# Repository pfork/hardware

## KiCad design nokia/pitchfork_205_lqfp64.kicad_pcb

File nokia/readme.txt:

cc0 licensed PITCHFORK board in nokia3310 formfactor

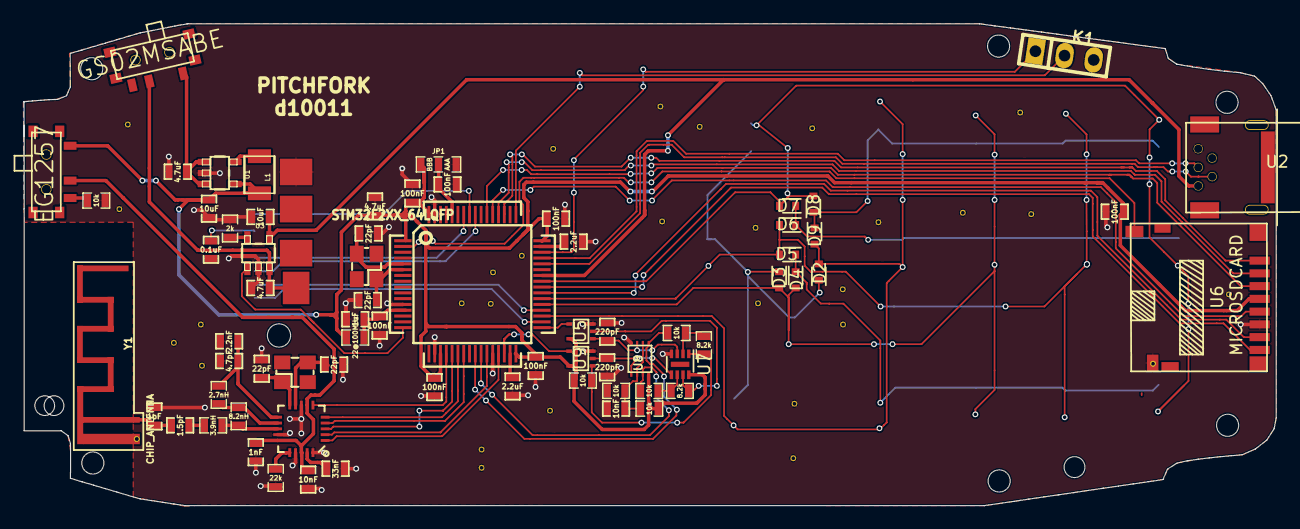
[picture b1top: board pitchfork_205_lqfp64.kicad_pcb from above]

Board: 2 copper layers, 108.0 x 41.5 mm, 100 parts (1 on the bottom side), 67 nets.

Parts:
1Pin_12mil_VIA, 1Pin_12mil_VIA#2, 1Pin_12mil_VIA#3, 1Pin_12mil_VIA#4, 1Pin_12mil_VIA#5, 1Pin_12mil_VIA#6, 1Pin_12mil_VIA#7, 1Pin_12mil_VIA#8, 1Pin_12mil_VIA#9, 1Pin_12mil_VIA#10, 1Pin_12mil_VIA#11, 1Pin_12mil_VIA#12, 1Pin_12mil_VIA#13, 1Pin_12mil_VIA#14, 1Pin_12mil_VIA#15, 1Pin_12mil_VIA#16, 1Pin_12mil_VIA#17, 1Pin_12mil_VIA#18, 1Pin_12mil_VIA#19, 1Pin_12mil_VIA#20, 1Pin_12mil_VIA#21, 1Pin_12mil_VIA#22, 1Pin_12mil_VIA#23, 1Pin_12mil_VIA#24, 1Pin_12mil_VIA#25, 1Pin_12mil_VIA#26, 1Pin_12mil_VIA#27, 1Pin_12mil_VIA#28, 1Pin_12mil_VIA#29: VAL**; 1Pin_12mil_VIA
B1: 3310
C1, C2, C25, C26: 22pF; SM0603_Opendous
C3, C4, C9, C10, C11, C14, C34: 100nF; SM0603_Opendous
C5, C6, C13: 4.7uF; SM0603_Opendous
C7, C8: 2.2uF; SM0603_Opendous
C12, C20: 10uF; SM0603_Opendous
C15: 1uF; SM0603_Opendous
C16, C19: 10nF; SM0603_Opendous
C17: 1nF; SM0603_Opendous
C18: 0.1uF; SM0603_Opendous
C21: 33nF; SM0603_Opendous
C22: 1pF; SM0603_Opendous
C23: 1.5pF; SM0603_Opendous
C24: 4.7pF; SM0603_Opendous
C27: 2.2nF; SM0603_Opendous
C28, C29: 220pF; SM0603_Opendous
D2, D3, D4, D5, D6, D7, D8, D9: 1N5148; SOD-523
IC1: STM32F2XX_64LQFP; LQFP64_Opendous
JP1: JUMPER3; 0603_Jumper
K1: CONN_3; pin_strip_3
L1: 10uH; SparkFun-1210
L2: 22@100MHz; 0603_Opendous
L5: 3.9nH; 0603_Opendous
L6: 8.2nH; 0603_Opendous
L7: 2.7nH; 0603_Opendous
R1, R5, R6, R9, R10, R11: 10k; 0603_Opendous
R3: 2k; 0603_Opendous
R4: 22k; 0603_Opendous
R7, R8: 8.2k; 0603_Opendous
SW_POWER1: GS02MSABE; EG1257
SW_RFPWR1: EG1257
U1: LM3670; SparkFun-SOT23-5
U2: USBCONN; miniusb
U3: MCP73832-2; SparkFun-SOT23-5
U4: NRF24L01+; QFN20_0.5mmPitch_HMC5843
U5, U9: MC74VHC1G66; SOT-353
U6: MICROSDCARD; HiroseDM3D-SF
U7: TSV912; DFN-8-1EP_2x2mm_Pitch0.5mm
U8: TC75W57; SSOP8-P0.5
X1: 25MHz; Crystal_3.2x2.5mm
X2: 16MHz; Crystal_3.2x2.5mm
Y1: CHIP_ANTENNA; Antenna_Meander_2.4GHz_TI_AN043

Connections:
/B0I: B1.25, B1.45, B1.47, B1.49, D7.2, D8.2, IC1.41
/B0O: B1.30, B1.36, B1.42, B1.46, D6.1, D7.1
/B1I: B1.19, B1.27, B1.29, B1.31, D2.2, D9.2, IC1.35
/B1O: B1.28, B1.34, B1.40, B1.50, D8.1, D9.1
/B3O: B1.32, B1.38, B1.44, B1.48, D4.1, D5.1
/B4I: B1.21, B1.33, B1.35, B1.37, D3.2, D4.2, IC1.37
/B7I: B1.23, B1.39, B1.41, B1.43, D5.2, D6.2, IC1.38
/BCO: B1.20, B1.22, B1.24, B1.26, D2.1, D3.1
/CHRG_STAT: IC1.16, U3.1
/LCD_CS: B1.13, IC1.58
/LCD_DC: B1.12, IC1.56
/LCD_RES: B1.16, IC1.57
/LCD_SCLK: B1.10, IC1.34
/LCD_SDIN: B1.11, IC1.36
/VBAT: C6.1, SW_POWER1.1, U1.1, U1.3
/VBAT0: B1.5, C5.1, SW_POWER1.2, U3.3
/comp1: IC1.25, R6.2, U8.1
/comp2: IC1.26, R9.2, U8.7
/nrf_ce: IC1.29, U4.1
/nrf_csn: IC1.27, U4.2
/nrf_irq: IC1.20, U4.6
/nrf_miso: IC1.22, U4.5
/nrf_mosi: IC1.23, U4.4
/nrf_sck: IC1.21, U4.3
/rswen1: IC1.33, U5.4
/rswen2: IC1.30, U9.4
/sd_cd: IC1.2, U6.10
/sd_clk: IC1.53, U6.5
/sd_cmd: IC1.54, U6.3
/sd_d0: IC1.39, U6.7
/sd_d1: IC1.40, U6.8
/sd_d2: IC1.51, U6.1
/sd_d3: IC1.52, U6.2
/swclk: IC1.49, K1.2
/swdio: IC1.46, K1.1
/usb_5v: C20.1, IC1.42, U2.1, U3.4
/usb_dm: IC1.44, U2.2
/usb_dp: IC1.45, U2.3
/vdd: B1.9, C4.1, C9.2, C10.2, C11.2, C12.1, C13.2, C34.2, IC1.1, IC1.19, IC1.32, IC1.48, IC1.64, JP1.3, L1.2, L2.2, R1.2, R10.1, SW_RFPWR1.2, U1.4, U5.5, U6.4, U7.8, U8.8, U9.5
GND: 1Pin_12mil_VIA.1, 1Pin_12mil_VIA#2.1, 1Pin_12mil_VIA#3.1, 1Pin_12mil_VIA#4.1, 1Pin_12mil_VIA#5.1, 1Pin_12mil_VIA#6.1, 1Pin_12mil_VIA#7.1, 1Pin_12mil_VIA#8.1, 1Pin_12mil_VIA#9.1, 1Pin_12mil_VIA#10.1, 1Pin_12mil_VIA#11.1, 1Pin_12mil_VIA#12.1, 1Pin_12mil_VIA#13.1, 1Pin_12mil_VIA#14.1, 1Pin_12mil_VIA#15.1, 1Pin_12mil_VIA#16.1, 1Pin_12mil_VIA#17.1, 1Pin_12mil_VIA#18.1, 1Pin_12mil_VIA#19.1, 1Pin_12mil_VIA#20.1, 1Pin_12mil_VIA#21.1, 1Pin_12mil_VIA#22.1, 1Pin_12mil_VIA#23.1, 1Pin_12mil_VIA#24.1, 1Pin_12mil_VIA#25.1, 1Pin_12mil_VIA#26.1, 1Pin_12mil_VIA#27.1, 1Pin_12mil_VIA#28.1, 1Pin_12mil_VIA#29.1, B1.8, B1.14, B1.17, B1.18, C1.1, C2.1, C3.2, C4.2, C5.2, C6.2, C7.2, C8.2, C9.1, C10.1, C11.1, C12.2, C13.1, C14.2, C15.2, C16.2, C17.2, C18.2, C19.2, C20.2, C21.1, C22.1, C24.1, C25.2, C26.2, C27.1, C28.2, C29.2, C34.1, IC1.12, IC1.18, IC1.28, IC1.63, JP1.1, K1.3, R3.2, R4.1, R5.2, R11.1, U1.2, U2.5, U3.2, U4.8, U4.14, U4.17, U4.20, U5.3, U6.6, U6.9, U7.4, U8.4, U9.3
unnamed: B1.15, C18.1
unnamed: C1.2, IC1.5, X1.2
unnamed: C2.2, IC1.6, X1.1
unnamed: C3.1, IC1.60, JP1.2
unnamed: C7.1, IC1.31
unnamed: C8.1, IC1.47
unnamed: C14.1, C15.1, IC1.13, L2.1
unnamed: C16.1, C17.1, SW_RFPWR1.1, U4.7, U4.15, U4.18
unnamed: C19.1, R1.1, R5.1, U8.2, U8.6
unnamed: C21.2, U4.19
unnamed: C22.2, C23.1, Y1.1
unnamed: C23.2, L5.1
unnamed: C24.2, C27.2, L7.2, U4.11
unnamed: C25.1, U4.9, X2.2
unnamed: C26.1, U4.10, X2.1
unnamed: C28.1, U5.1, U7.3, U8.3
unnamed: C29.1, U7.5, U8.5, U9.2
unnamed: L1.1, U1.5
unnamed: L5.2, L6.2, U4.13
unnamed: L6.1, L7.1, U4.12
unnamed: R3.1, U3.5
unnamed: R4.2, U4.16
unnamed: R6.1, R7.2, U7.2
unnamed: R8.1, U5.2, U7.7
unnamed: R8.2, R9.1, U7.6
unnamed: R7.1, R10.2, U7.1, U9.1
unnamed: R11.2, SW_RFPWR1.3

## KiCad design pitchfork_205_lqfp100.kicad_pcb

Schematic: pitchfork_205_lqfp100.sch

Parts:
BT1: BATTERY_LI-ION
C1: 4.7uF
C2, C22: 10uF
C3, C20: 22p
C4, C15, C16, C17, C18, C19, C25, C27, C29: 100n
C5: 100n
C6, C7, C30: 100nF
C21: 4.7u
C23, C24: 2.2u
C26, C28: 1u
C31: 10pF
C32: 33nF
C33, C34: 22pF
C35: CSMALL
C36: 1.5pF
C37: 4.7pF
C38: 2.2nF
C39, C41, C43: 2.2uF
C40, C42: 0.1uF
D1: SML-211UTT86
D2: SML-211YTT86
D3, D4: SML-211UTT86
JP2: JUMPER
L1: 30@100MHz
L2: 22@100MHz
L3: FERRITE
L4: 3.9nH
L5: 8.2nH
L6: 2.7nH
L7: 10uH
P1: SD_CARD
R1, R2: 1k
R3: R1002-1%63
R4: 22k
R6: 2k
R7: 560k
R13, R14: 1k
SW1, SW2, SW3, SW4: SW_PUSH
SW5: SWITCH_PUSHBUTTON
U1: STM32F205Vxx
U2: NRF24L01+
U3: USBCONN
U4: LM3670
U5: MCP73832-2
U6: UG-2864H
X1: CRYSTAL
X2: 3.2x2.5
Y1: CHIP_ANTENNA

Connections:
+5V: C22.1, U3.1 (VBUS), U5.4 (VDD)
/3V3_adc: C25.1, C26.1, C27.1, C28.1, L2.2, U1.21, U1.22
/+3.7V: BT1.1 (+), C1.1, U4.1 (VIN), U4.3 (EN)
/BAT_CHRG: BT1.3 (Ts), U5.3 (VBAT)
/boot0: C4.2, JP2.1, U1.94
/btn0: SW1.1, U1.58
/btn1: SW2.1, U1.57
/btn2: SW3.1, U1.56
/btn3: SW4.1, U1.55
/lcd_cs: U1.88, U6.13 (CS#)
/lcd_d0: U1.61, U6.18 (D0)
/lcd_d1: U1.62, U6.19 (D1)
/lcd_d2: U1.81, U6.20 (D2)
/lcd_d3: U1.82, U6.21 (D3)
/lcd_d4: U1.38, U6.22 (D4)
/lcd_d5: U1.39, U6.23 (D5)
/lcd_d6: U1.40, U6.24 (D6)
/lcd_d7: U1.41, U6.25 (D7)
/lcd_rd: U1.85, U6.17 (E/RD#)
/lcd_res: U1.5, U6.14 (RES#)
/lcd_w: U1.86, U6.16 (R/W#)
/led_mode: R1.1, U1.24
/led_read: R13.1, U1.26
/led_status: R2.1, U1.23
/led_write: R14.1, U1.25
/nrf_ce: U1.36, U2.1 (CE)
/nrf_csn: R3.1, U1.37, U2.2 (CSN)
/nrf_irq: U1.35, U2.6 (IRQ)
/nrf_miso: U1.31, U2.5 (MISO)
/nrf_mosi: U1.32, U2.4 (MOSI)
/nrf_sck: U1.30, U2.3 (SCK)
/nrst: C29.2, SW5.1 (A), U1.14
/osc_in: C3.1, U1.12, X1.2
/osc_out: C20.1, U1.13, X1.1
/sd_cd: U1.7
/sd_clk: P1.5 (CLK), U1.80
/sd_cmd: P1.3 (CMD/DI), U1.83
/sd_d0: P1.7 (DAT0/DO), U1.65
/sd_d1: P1.8 (DAT1), U1.66
/sd_d2: P1.1 (DAT2), U1.78
/sd_d3: P1.2 (DAT3/CS), U1.79
/usb_dm: U1.70, U3.2 (DN)
/usb_dp: U1.71, U3.3 (DP)
/vcap_1: C23.1, U1.49
/vcap_2: C24.1, U1.73
unnamed: C6.2, C7.2, C30.2, C31.2, L3.2, R3.2, U2.7 (VDD), U2.15 (VDD), U2.18 (VDD)
unnamed: R4.2, U2.16 (IREF)
unnamed: L4.2, L5.2, U2.13 (ANT2)
unnamed: C35.2, C36.1, Y1.1
unnamed: C36.2, L4.1
unnamed: D2.1 (A), R2.2
unnamed: R7.1 (A), U6.26 (IREF)
unnamed: C43.1, U6.27 (VCOMH)
unnamed: D4.1 (A), R14.2
unnamed: C37.2, C38.2, L6.2, U2.11 (VDD_PA)
unnamed: L5.1, L6.1, U2.12 (ANT1)
unnamed: D3.1 (A), R13.2
unnamed: D1.1 (A), R1.2
unnamed: L1.1, U3.5 (SHIELD)
unnamed: R6.1, U5.5 (PROG)
unnamed: L7.1, U4.5 (SW)
unnamed: C32.2, U2.19 (DVDD)
unnamed: C34.1, U2.10 (XC1), X2.1
unnamed: C33.1, U2.9 (XC2), X2.2

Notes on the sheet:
POWER
BATTERY CHARGER
RADIO
BUTTONS
USB
LEDS
LCD

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
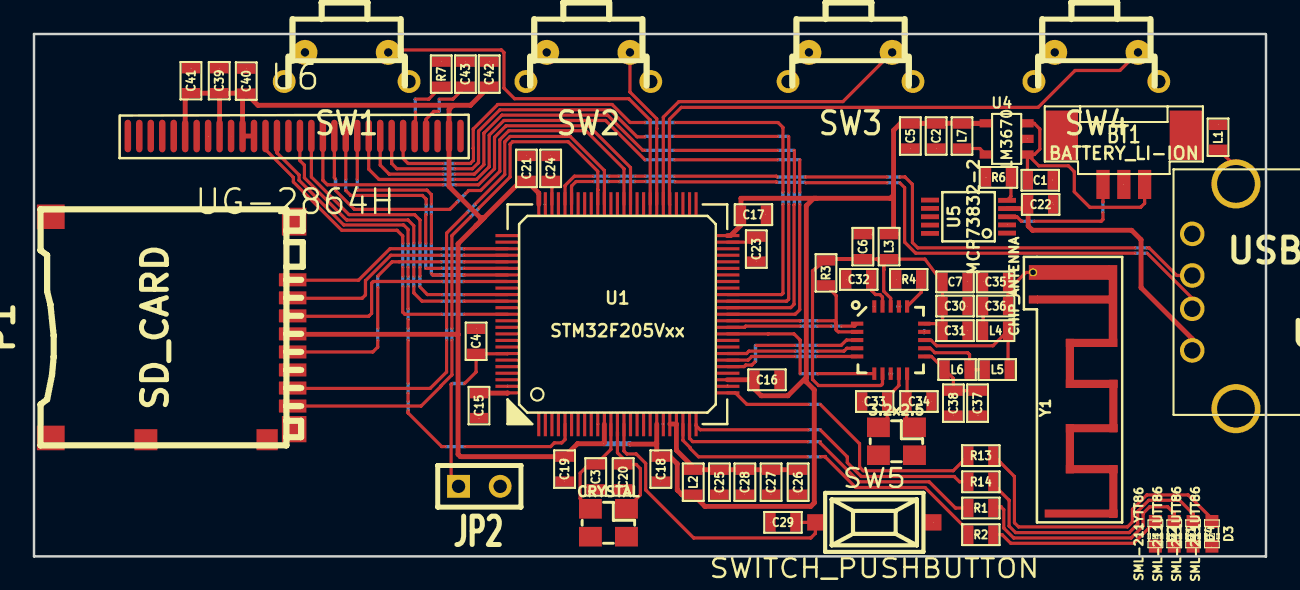
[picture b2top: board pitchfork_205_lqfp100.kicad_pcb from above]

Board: 2 copper layers, 75.2 x 31.9 mm, 72 parts (0 on the bottom side), 65 nets.

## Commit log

2014-02-22 [enh] initial commit - traces needed
2014-02-26 [enh] 1st review, traces drawn
2014-04-03 [enh] finished backloading sd version
2017-02-26 [enh] 1st revision of board - base for 2nd pcb order
2017-03-04 [mod] removed obsolete kicad project file
2017-03-04 [enh] added panelized version of baseboard
2017-03-04 [mod] moved baseboard files into board/small
2017-03-04 [mod] added fp-lib-table to baseboard
2017-03-04 [enh] added gerberfiles of v2 baseboard
2017-03-04 [mod] update after kicad upgrade of baseboard
2017-03-04 [enh] added BoM for v2 and v3310
2017-03-04 [enh] added 3310 version
2017-03-04 [mod] added also fp-lib-table for 3310
2017-04-05 [fix] bugs from 2nd revision fixed
2017-04-05 [mod] added new .xml file
2017-04-07 [fix] outer rings for buttons on nokia board
2017-04-16 [fix] lcd pinout + added R for nrf switch
2017-04-26 [fix] corrected rf powerswitch + r11
2017-04-27 [enh] added enclosure prototype
2017-04-28 [enh] added measurements of peripherials affecting enclosure to pcb
2017-04-29 [enh] Library cleanup: removed Worldsemi and didoe references, updated rescue cache
2017-04-29 [fix] added SD card detect GND pin to sch
2017-04-29 [enh] ignored backup files
2017-04-29 [mod] more gitignore
2017-04-29 [fix] SD card detect GND via under pin 9 (+netlist update)
2017-04-29 [mod] kicad drives me nuts with its temp files
2017-04-29 [enh] removed Worldsemi and didoe references, but now in the small version
2017-04-29 [mod] zone refill
2017-05-14 [mod] attributed source for enclosure
2017-11-27 [mod] final version
2017-11-27 [mod] switching to blender for case design
2018-01-14 [mod] button schema beautified in nokia
